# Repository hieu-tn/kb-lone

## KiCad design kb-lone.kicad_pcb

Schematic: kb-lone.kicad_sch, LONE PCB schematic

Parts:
C1, C3, C17, C18: 100n; C_0805_2012Metric
C2: 10u; C_0805_2012Metric
C4, C5: 1u; C_0805_2012Metric
C6, C7, C8, C14, C15: 100n; C_0402_1005Metric
C9, C10: 12p; C_0402_1005Metric
C11, C16: 4.7u; C_0402_1005Metric
C12: 10n; C_0402_1005Metric
C13: 10u; CP_EIA-3216-10_Kemet-I_Pad1.58x1.35mm_HandSolder
C19, C20, C21, C22, C23, C24, C25, C26, C27, C28, C29, C30, C31, C32, C33, C34, C35, C36, C37, C38, C39, C40, C41, C42, C43, C44, C45, C46, C47, C48, C49, C50, C51, C52, C53, C54, C55, C56, C57, C58, C59, C60, C61, C62, C63, C64, C65, C66, C67, C68, C69, C70, C71, C72, C73, C74, C75, C76, C77, C78, C79, C80, C81, C82, C83, C84, C85, C86, C87, C88, C89, C90, C91, C92, C93, C94, C95, C96, C97, C98, C99, C100: 100n; C_0402_1005Metric_1
D1, D3, D4, D5, D6, D7, D8, D9, D10, D11, D12, D13, D14, D15, D16, D17, D18, D19, D20, D21, D22, D23, D24, D25, D26, D27, D28, D29, D30, D31, D32, D33, D34, D35, D36, D37, D38, D39, D40, D41, D42, D43, D44, D45, D46, D47, D48, D49, D50, D51, D52, D53, D54, D55, D56, D57, D58, D59, D60, D61, D62, D63, D64, D65, D66, D67, D68, D69, D70, D71, D72, D73, D74, D75, D76, D77, D78, D79, D80, D81, D82, D83, D84: 1N4148W; D_SOD-123
D2: RB060M-60TR; D_SOD-123; Manufacturer Part Number RB060M-60TR
D85, D86, D87, D88, D89, D90, D91, D92, D93, D94, D95, D96, D97, D98, D99, D100, D101, D102, D103, D104, D105, D106, D107, D108, D109, D110, D111, D112, D113, D114, D115, D116, D117, D118, D119, D120, D121, D122, D123, D124, D125, D126, D127, D128, D129, D130, D131, D132, D133, D134, D135, D136, D137, D138, D139, D140, D141, D142, D143, D144, D145, D146, D147, D148, D149, D150, D151, D152, D153, D154, D155, D156, D157, D158, D159, D160, D161, D162, D163, D164, D165, D166: SK6812MINI-E; SK6812MINI_3535_6028_3.2x2.8mm_Round; Manufacturer Part Number SK812MINI-E
F1: mSMD110-16V; Fuse_1812_4532Metric; Manufacturer Part Number mSMD110-16V
FB1, FB2: CBW201209U121T; L_0805_2012Metric; Manufacturer Part Number CBW201209U121T
H1, H2, H3, H4, H5, H6, H7, H8: 9774035243R; Manufacturer Part Number 9774030243R
H9: MountingHole; MountingHole_2.5x4.0mm
J1: TYPE-C-31-M12; TYPE-C-31-M-12; Manufacturer Part Number TYPE-C-31-M-12
J2, J3: SM04B-SRSS-TB(LF)(SN); SM04B-SRSS-TB(LF)(SN)_mounting-reliefs; Manufacturer Part Number SM04B-SRSS-TB(LF)(SN)
J4: SSD1306
M1: RGB DB notch; rgb_daughterboard_notch_plated_8x4mm
Q1: DTC123JKAT146; SOT-23; Manufacturer Part Number DTC123JKAT146
R1, R2: 5.1k; R_0805_2012Metric
R3: 100R; R_0805_2012Metric
R4: 330k; R_0805_2012Metric
R5: 1M; R_0805_2012Metric
R6, R7: 100k; R_0805_2012Metric
R8, R12, R14: 10k; R_0805_2012Metric
R9, R10: 4.7k; R_0402_1005Metric
R11: 4.7k; R_0805_2012Metric
R13: 1.5k; R_0402_1005Metric
R15, R16, R17, R18, R19, R20, R21, R22, R23, R24, R25, R26, R27, R28, R29, R30, R31, R32, R33, R34, R35, R36, R37, R38, R39, R40, R41, R42, R43, R44, R45, R46, R47, R48, R49, R50, R51, R52, R53, R54, R55, R56, R57, R58, R59, R60, R61, R62, R63, R64, R65, R66, R67, R68, R69, R70, R71, R72, R73, R74, R75, R76, R77, R78, R79, R80, R81, R82, R83, R84, R85, R86, R87, R88, R89, R90, R91, R92, R93, R94, R95, R96: 5.1R; R_0402_1005Metric_1
SW1: K2-1187SQ-A4SW-06; Manufacturer Part Number K2-1187SQ-A4SW-06
SW2: ESC; MX100H; Manufacturer Part Number CPG151101S11
SW3: F1; MX100H; Manufacturer Part Number CPG151101S11
SW4: F2; MX100H; Manufacturer Part Number CPG151101S11
SW5: F3; MX100H; Manufacturer Part Number CPG151101S11
SW6: F4; MX100H; Manufacturer Part Number CPG151101S11
SW7: F5; MX100H; Manufacturer Part Number CPG151101S11
SW8: F6; MX100H; Manufacturer Part Number CPG151101S11
SW9: F7; MX100H; Manufacturer Part Number CPG151101S11
SW10: F8; MX100H; Manufacturer Part Number CPG151101S11
SW11: F9; MX100H; Manufacturer Part Number CPG151101S11
SW12: F10; MX100H; Manufacturer Part Number CPG151101S11
SW13: F11; MX100H; Manufacturer Part Number CPG151101S11
SW14: F12; MX100H; Manufacturer Part Number CPG151101S11
SW15: KNOB; MXA100; Manufacturer Part Number CPG151101S11
SW16: GRV; MX100H; Manufacturer Part Number CPG151101S11
SW17: 1; MX100H; Manufacturer Part Number CPG151101S11
SW18: 2; MX100H; Manufacturer Part Number CPG151101S11
SW19: 3; MX100H; Manufacturer Part Number CPG151101S11
SW20: 4; MX100H; Manufacturer Part Number CPG151101S11
SW21: 5; MX100H; Manufacturer Part Number CPG151101S11
SW22: 6; MX100H; Manufacturer Part Number CPG151101S11
SW23: 7; MX100H; Manufacturer Part Number CPG151101S11
SW24: 8; MX100H; Manufacturer Part Number CPG151101S11
SW25: 9; MX100H; Manufacturer Part Number CPG151101S11
SW26: 0; MX100H; Manufacturer Part Number CPG151101S11
SW27: MINUS; MX100H; Manufacturer Part Number CPG151101S11
SW28: EQUAL; MX100H; Manufacturer Part Number CPG151101S11
SW29: BSPC; MX200H; Manufacturer Part Number CPG151101S11
SW30, SW45: N/A; MX100H; Manufacturer Part Number CPG151101S11
SW31: TAB; MX150H; Manufacturer Part Number CPG151101S11
SW32: Q; MX100H; Manufacturer Part Number CPG151101S11
SW33: W; MX100H; Manufacturer Part Number CPG151101S11
SW34: E; MX100H; Manufacturer Part Number CPG151101S11
SW35: R; MX100H; Manufacturer Part Number CPG151101S11
SW36: T; MX100H; Manufacturer Part Number CPG151101S11
SW37: Y; MX100H; Manufacturer Part Number CPG151101S11
SW38: U; MX100H; Manufacturer Part Number CPG151101S11
SW39: I; MX100H; Manufacturer Part Number CPG151101S11
SW40: O; MX100H; Manufacturer Part Number CPG151101S11
SW41: P; MX100H; Manufacturer Part Number CPG151101S11
SW42: LBRKT; MX100H; Manufacturer Part Number CPG151101S11
SW43: RBRKT; MX100H; Manufacturer Part Number CPG151101S11
SW44: BSLS; MX150H; Manufacturer Part Number CPG151101S11
SW46: CAPS; MX175H; Manufacturer Part Number CPG151101S11
SW47: A; MX100H; Manufacturer Part Number CPG151101S11
SW48: S; MX100H; Manufacturer Part Number CPG151101S11
SW49: D; MX100H; Manufacturer Part Number CPG151101S11
SW50: F; MX100H; Manufacturer Part Number CPG151101S11
SW51: G; MX100H; Manufacturer Part Number CPG151101S11
SW52: H; MX100H; Manufacturer Part Number CPG151101S11
SW53: J; MX100H; Manufacturer Part Number CPG151101S11
SW54: K; MX100H; Manufacturer Part Number CPG151101S11
SW55: L; MX100H; Manufacturer Part Number CPG151101S11
SW56: COLON; MX100H; Manufacturer Part Number CPG151101S11
SW57: QUOTE; MX100H; Manufacturer Part Number CPG151101S11
SW58: ENTER; MX225HR; Manufacturer Part Number CPG151101S11
SW59: PGUP; MX100H; Manufacturer Part Number CPG151101S11
SW60: LSHFT; MX225H; Manufacturer Part Number CPG151101S11
SW61: Z; MX100H; Manufacturer Part Number CPG151101S11
SW62: X; MX100H; Manufacturer Part Number CPG151101S11
SW63: C; MX100H; Manufacturer Part Number CPG151101S11
SW64: V; MX100H; Manufacturer Part Number CPG151101S11
SW65: B; MX100H; Manufacturer Part Number CPG151101S11
SW66: N; MX100H; Manufacturer Part Number CPG151101S11
SW67: M; MX100H; Manufacturer Part Number CPG151101S11
SW68: COMMA; MX100H; Manufacturer Part Number CPG151101S11
SW69: DOT; MX100H; Manufacturer Part Number CPG151101S11
SW70: SLSH; MX100H; Manufacturer Part Number CPG151101S11
SW71: RSHFT; MX175H; Manufacturer Part Number CPG151101S11
SW72: UP; MX100H; Manufacturer Part Number CPG151101S11
SW73: PGDN; MX100H; Manufacturer Part Number CPG151101S11
SW74: LCTRL; MX125H; Manufacturer Part Number CPG151101S11
SW75: WIN; MX125H; Manufacturer Part Number CPG151101S11
SW76: LALT; MX125H; Manufacturer Part Number CPG151101S11
SW77: SPACE; MX625HR; Manufacturer Part Number CPG151101S11
SW78: RALT; MX100H; Manufacturer Part Number CPG151101S11
SW79: FN; MX100H; Manufacturer Part Number CPG151101S11
SW80: RCTRL; MX100H; Manufacturer Part Number CPG151101S11
SW81: LEFT; MX100H; Manufacturer Part Number CPG151101S11
SW82: DOWN; MX100H; Manufacturer Part Number CPG151101S11
SW83: RIGHT; MX100H; Manufacturer Part Number CPG151101S11
SW84: RotaryEncoder_Switch; PEC11R-4220K-S0024
U1: USBLC6-2SC6; SOT-23-6; Manufacturer Part Number USBLC6-2SC6
U2: MCP1700T-3302E/TT; SOT-23; Manufacturer Part Number MCP1700T-3302E/TT
U3: BL24C256A-SFRC; TSSOP-8_4.4x3mm_P0.65mm; Manufacturer Part Number BL24C256A-SFRC
U4: STM32F401RCT6; LQFP-64_10x10mm_P0.5mm; Manufacturer Part Number STM32F401RBT6
U5: TXS0101DBVR; SOT-23-6; Manufacturer Part Number TXS0101DBVR
X1: USB pins; PinHeader_1x4_P2.54mm_Vertical
Y1: TAXM8M4RFDCET2T; Crystal_SMD_3225-4Pin_3.2x2.5mm; Manufacturer Part Number TAXM8M4RFDCET2T

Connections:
3V3: C3.2, C5.1, C6.2, C7.1, C8.1, C11.2, C12.2, C13.1, C14.2, C15.2, C17.2, D2.2 (A), J4.3 (VCC), R7.1, R9.2, R10.2, R13.1, R14.1, SW1.1 (A), U2.2 (VO), U3.8 (VCC), U4.1 (VBAT), U4.13 (VDDA/VREF+), U4.19 (VDD), U4.32 (VDD), U4.48 (VDD), U4.64 (VDD), U5.1 (VCCA)
5V: C4.1, C18.1, D2.1 (K), F1.2, J2.1, J3.1, R6.1, R11.2, R15.2, R16.2, R17.2, R18.2, R19.2, R20.2, R21.2, R22.2, R23.2, R24.2, R25.2, R26.2, R27.2, R28.2, R29.2, R30.2, R31.2, R32.2, R33.2, R34.2, R35.2, R36.2, R37.2, R38.2, R39.2, R40.2, R41.2, R42.2, R43.2, R44.2, R45.2, R46.2, R47.2, R48.2, R49.2, R50.2, R51.2, R52.2, R53.2, R54.2, R55.2, R56.2, R57.2, R58.2, R59.2, R60.2, R61.2, R62.2, R63.2, R64.2, R65.2, R66.2, R67.2, R68.2, R69.2, R70.2, R71.2, R72.2, R73.2, R74.2, R75.2, R76.2, R77.2, R78.2, R79.2, R80.2, R81.2, R82.2, R83.2, R84.2, R85.2, R86.2, R87.2, R88.2, R89.2, R90.2, R91.2, R92.2, R93.2, R94.2, R95.2, R96.2, U2.3 (VI), U5.6 (VCCB), X1.1
BOOT0: C2.2, R4.2, R5.2, U4.60 (BOOT0)
C0: SW2.2, SW16.2, SW31.2, SW46.2, SW60.2, SW74.2, U4.35 (SPI2_MISO/PB14)
C1: SW3.1, SW17.1, SW32.1, SW47.1, SW75.1, U4.36 (SPI2_MOSI/PB15)
C2: SW4.1, SW18.1, SW33.1, SW48.1, SW61.1, SW76.1, U4.37 (I2S2_MCK/TIM3_CH1/USART6_TX/PC6)
C3: SW5.1, SW19.1, SW34.1, SW49.1, SW62.1, U4.38 (USART6_RX/TIM3_CH2/PC7)
C4: SW6.1, SW20.1, SW35.1, SW50.1, SW63.1, U4.39 (USART6_CK/TIM3_CH3/PC8)
C5: SW7.1, SW21.1, SW36.1, SW51.1, SW64.1, U4.40 (TIM3_CH4/I2S_CKIN/PC9)
C6: SW8.1, SW22.1, SW37.1, SW52.1, SW65.1, SW77.2, U4.41 (USART1_CK/TIM1_CH1/PA8)
C7: SW9.1, SW23.1, SW38.1, SW53.1, SW66.1, U4.43 (USART1_RX/TIM1_CH3/PA10)
C8: SW10.1, SW24.1, SW39.1, SW54.1, SW67.1, U4.52 (SPI3_MISO/PC11)
C9: SW11.1, SW25.1, SW40.1, SW55.1, SW68.1, SW78.2, U4.53 (SPI3_MOSI/PC12)
C10: SW12.1, SW26.1, SW41.1, SW56.1, SW69.1, SW79.1, U4.54 (PD2)
C11: SW13.1, SW27.1, SW42.1, SW57.1, SW70.1, SW80.1, U4.55 (JTDO-SWO/SPI1_SCK/SPI3_SCK/I2C2_SDA/TIM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)
C12: SW14.1, SW28.1, SW43.1, SW58.1, SW71.1, SW81.1, U4.56 (NJTRST/SPI1_MISO/SPI3_MISO/I2C3_SDA/TIM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)
C13: SW29.1, SW44.1, SW72.1, SW82.1, U4.57 (SPI1_MOSI/SPI3_MOSI/TIM3_CH2/PB5)
C14: SW15.1, SW30.1, SW45.1, SW59.1, SW73.1, SW83.1, U4.16 (PA2/USART2_TX)
D+: J2.3, R13.2, U1.3 (I/O2), U4.45 (OTG_FS_DP/USART6_RX/PA12), X1.3
D-: J2.2, U1.1 (I/O1), U4.44 (OTG_FS_DM/TIM1_CH4/USART6_TX/PA11), X1.2
DBUS+: J1.A6 (D+), J1.B6 (D+), U1.4 (I/O2)
DBUS-: J1.A7 (D-), J1.B7 (D-), U1.6 (I/O1)
ENC_A: SW84.A, U4.51 (SPI3_SCK/I2S3_CK/PC10)
ENC_B: SW84.B, U4.50 (JTDI/TIM2_CH1/PA14)
E_PA3: U4.17 (PA3/TIM2_CH4)
E_PA4: U4.20 (PA4/USART2_CK)
E_PA5: U4.21 (PA5/TIM2_CH1/SPI1_SCK)
E_PA6: U4.22 (PA6/TIM3_CH1/SPI1_MISO)
E_PA7: U4.23 (PA7/SPI1_MOSI/TIM3_CH2)
E_PB0: U4.26 (PB0/TIM3_CH3)
E_PB1: U4.27 (PB1/TIM3_CH4)
E_PB9: U4.62 (I2C1_SDA/TIM4_CH4/TIM11_CH1/PB9)
E_PB10: U4.29 (PB10/TIM2_CH3/SPI2_SCK/I2C2_SCL/I2S2_CK)
E_PB12: U4.33 (PB12)
E_PB13: U4.34 (SPI2_SCK/I2S2_CK/PB13)
E_PC4: U4.24 (PC4)
E_PC5: U4.25 (PC5)
E_PC13: U4.2 (PC13)
GNDPWR: FB2.2, H9.1, J1.S (SHIELD)
I2C_CLK: J4.2 (SCL), U4.4 (PC15/OSC32_OUT)
I2C_DAT: J4.1 (SDA), U4.3 (PC14/OSC32_IN)
NRST: C1.1, R3.2, U4.7 (NRST)
unnamed: C16.2, U4.30 (VCAP1)
unnamed: C19.1, D85.1 (VDD), R15.1
unnamed: C20.1, D86.1 (VDD), R16.1
unnamed: C21.1, D87.1 (VDD), R17.1
unnamed: C22.1, D88.1 (VDD), R18.1
unnamed: C23.1, D89.1 (VDD), R19.1
unnamed: C24.1, D90.1 (VDD), R20.1
unnamed: C25.1, D91.1 (VDD), R21.1
unnamed: C26.1, D92.1 (VDD), R22.1
unnamed: C27.1, D93.1 (VDD), R23.1
unnamed: C28.1, D94.1 (VDD), R24.1
unnamed: C29.1, D95.1 (VDD), R25.1
unnamed: C30.1, D96.1 (VDD), R26.1
unnamed: C31.1, D97.1 (VDD), R27.1
unnamed: C32.1, D98.1 (VDD), R28.1
unnamed: C33.1, D99.1 (VDD), R29.1
unnamed: C34.1, D100.1 (VDD), R30.1
unnamed: C35.1, D101.1 (VDD), R31.1
unnamed: C36.1, D102.1 (VDD), R32.1
unnamed: C37.1, D103.1 (VDD), R33.1
unnamed: C38.1, D104.1 (VDD), R34.1
unnamed: C39.1, D105.1 (VDD), R35.1
unnamed: C40.1, D106.1 (VDD), R36.1
unnamed: C41.1, D107.1 (VDD), R37.1
unnamed: C42.1, D108.1 (VDD), R38.1
unnamed: C43.1, D109.1 (VDD), R39.1
unnamed: C44.1, D110.1 (VDD), R40.1
unnamed: C45.1, D111.1 (VDD), R41.1
unnamed: C46.1, D112.1 (VDD), R42.1
unnamed: C47.1, D113.1 (VDD), R43.1
unnamed: C48.1, D114.1 (VDD), R44.1
unnamed: C49.1, D115.1 (VDD), R45.1
unnamed: C50.1, D116.1 (VDD), R46.1
unnamed: C51.1, D117.1 (VDD), R47.1
unnamed: C52.1, D118.1 (VDD), R48.1
unnamed: C53.1, D119.1 (VDD), R49.1
unnamed: C54.1, D120.1 (VDD), R50.1
unnamed: C55.1, D121.1 (VDD), R51.1
unnamed: C56.1, D122.1 (VDD), R52.1
unnamed: C57.1, D123.1 (VDD), R53.1
unnamed: C58.1, D124.1 (VDD), R54.1
unnamed: C59.1, D125.1 (VDD), R55.1
unnamed: C60.1, D126.1 (VDD), R56.1
unnamed: C61.1, D127.1 (VDD), R57.1
unnamed: C62.1, D128.1 (VDD), R58.1
unnamed: C63.1, D129.1 (VDD), R59.1
unnamed: C64.1, D130.1 (VDD), R60.1
unnamed: C65.1, D131.1 (VDD), R61.1
unnamed: C66.1, D132.1 (VDD), R62.1
unnamed: C67.1, D133.1 (VDD), R63.1
unnamed: C68.1, D134.1 (VDD), R64.1
unnamed: C69.1, D135.1 (VDD), R65.1
unnamed: C70.1, D136.1 (VDD), R66.1
unnamed: C71.1, D137.1 (VDD), R67.1
unnamed: C72.1, D138.1 (VDD), R68.1
unnamed: C73.1, D139.1 (VDD), R69.1
unnamed: C74.1, D140.1 (VDD), R70.1
unnamed: C75.1, D141.1 (VDD), R71.1
unnamed: C76.1, D142.1 (VDD), R72.1
unnamed: C77.1, D143.1 (VDD), R73.1
unnamed: C78.1, D144.1 (VDD), R74.1
unnamed: C79.1, D145.1 (VDD), R75.1
unnamed: C80.1, D146.1 (VDD), R76.1
unnamed: C81.1, D147.1 (VDD), R77.1
unnamed: C82.1, D148.1 (VDD), R78.1
unnamed: C83.1, D149.1 (VDD), R79.1
unnamed: C84.1, D150.1 (VDD), R80.1
unnamed: C85.1, D151.1 (VDD), R81.1
unnamed: C86.1, D152.1 (VDD), R82.1
unnamed: C87.1, D153.1 (VDD), R83.1
unnamed: C88.1, D154.1 (VDD), R84.1
unnamed: C89.1, D155.1 (VDD), R85.1
unnamed: C90.1, D156.1 (VDD), R86.1
unnamed: C91.1, D157.1 (VDD), R87.1
unnamed: C92.1, D158.1 (VDD), R88.1
unnamed: C93.1, D159.1 (VDD), R89.1
unnamed: C94.1, D160.1 (VDD), R90.1
unnamed: C95.1, D161.1 (VDD), R91.1
unnamed: C96.1, D162.1 (VDD), R92.1
unnamed: C97.1, D163.1 (VDD), R93.1
unnamed: C98.1, D164.1 (VDD), R94.1
unnamed: C99.1, D165.1 (VDD), R95.1
unnamed: C100.1, D166.1 (VDD), R96.1
unnamed: D1.1 (K), R4.1
unnamed: D1.2 (A), Q1.1 (B), SW1.2 (B)
unnamed: D3.2 (A), SW2.1
unnamed: D4.2 (A), SW3.2
unnamed: D5.2 (A), SW4.2
unnamed: D6.2 (A), SW5.2
unnamed: D7.2 (A), SW6.2
unnamed: D8.2 (A), SW7.2
unnamed: D9.2 (A), SW8.2
unnamed: D10.2 (A), SW9.2
unnamed: D11.2 (A), SW10.2
unnamed: D12.2 (A), SW11.2
unnamed: D13.2 (A), SW12.2
unnamed: D14.2 (A), SW13.2
unnamed: D15.2 (A), SW14.2
unnamed: D17.2 (A), SW16.1
unnamed: D18.2 (A), SW17.2
unnamed: D19.2 (A), SW18.2
unnamed: D20.2 (A), SW19.2
unnamed: D21.2 (A), SW20.2
unnamed: D22.2 (A), SW21.2
unnamed: D23.2 (A), SW22.2
unnamed: D24.2 (A), SW23.2
unnamed: D25.2 (A), SW24.2
unnamed: D26.2 (A), SW25.2
unnamed: D27.2 (A), SW26.2
unnamed: D28.2 (A), SW27.2
unnamed: D29.2 (A), SW28.2
unnamed: D30.2 (A), SW29.2
unnamed: D31.2 (A), SW30.2
unnamed: D32.2 (A), SW31.1
unnamed: D33.2 (A), SW32.2
unnamed: D34.2 (A), SW33.2
unnamed: D35.2 (A), SW34.2
unnamed: D36.2 (A), SW35.2
unnamed: D37.2 (A), SW36.2
unnamed: D38.2 (A), SW37.2
unnamed: D39.2 (A), SW38.2
unnamed: D40.2 (A), SW39.2
unnamed: D41.2 (A), SW40.2
unnamed: D42.2 (A), SW41.2
unnamed: D43.2 (A), SW42.2
unnamed: D44.2 (A), SW43.2
unnamed: D45.2 (A), SW44.2
unnamed: D46.2 (A), SW45.2
unnamed: D47.2 (A), SW46.1
unnamed: D48.2 (A), SW47.2
unnamed: D49.2 (A), SW48.2
unnamed: D50.2 (A), SW49.2
unnamed: D51.2 (A), SW50.2
unnamed: D52.2 (A), SW51.2
unnamed: D53.2 (A), SW52.2
unnamed: D54.2 (A), SW53.2
unnamed: D55.2 (A), SW54.2
unnamed: D56.2 (A), SW55.2
unnamed: D57.2 (A), SW56.2
unnamed: D58.2 (A), SW57.2
unnamed: D59.2 (A), SW58.2
unnamed: D60.2 (A), SW59.2
unnamed: D61.2 (A), SW60.1
unnamed: D62.2 (A), SW61.2
unnamed: D63.2 (A), SW62.2
unnamed: D64.2 (A), SW63.2
unnamed: D65.2 (A), SW64.2
unnamed: D66.2 (A), SW65.2
unnamed: D67.2 (A), SW66.2
unnamed: D68.2 (A), SW67.2
unnamed: D69.2 (A), SW68.2
unnamed: D70.2 (A), SW69.2
unnamed: D71.2 (A), SW70.2
unnamed: D72.2 (A), SW71.2
unnamed: D73.2 (A), SW72.2
unnamed: D74.2 (A), SW73.2
unnamed: D75.2 (A), SW74.1
unnamed: D76.2 (A), SW75.2
unnamed: D77.2 (A), SW76.2
unnamed: D78.2 (A), SW77.1
unnamed: D79.2 (A), SW78.1
unnamed: D80.2 (A), SW79.2
unnamed: D81.2 (A), SW80.2
unnamed: D82.2 (A), SW81.2
unnamed: D83.2 (A), SW82.2
unnamed: D84.2 (A), SW83.2
unnamed: D85.2 (DOUT), D99.4 (DIN)
unnamed: D85.4 (DIN), D86.2 (DOUT)
unnamed: D86.4 (DIN), D87.2 (DOUT)
unnamed: D87.4 (DIN), D88.2 (DOUT)
unnamed: D88.4 (DIN), D89.2 (DOUT)
unnamed: D89.4 (DIN), D90.2 (DOUT)
unnamed: D90.4 (DIN), D91.2 (DOUT)
unnamed: D91.4 (DIN), D92.2 (DOUT)
unnamed: D92.4 (DIN), D93.2 (DOUT)
unnamed: D93.4 (DIN), D94.2 (DOUT)
unnamed: D94.4 (DIN), D95.2 (DOUT)
unnamed: D95.4 (DIN), D96.2 (DOUT)
unnamed: D96.4 (DIN), D97.2 (DOUT)
unnamed: D97.4 (DIN), D98.2 (DOUT)
unnamed: D100.2 (DOUT), D101.4 (DIN)
unnamed: D99.2 (DOUT), D100.4 (DIN)
unnamed: D101.2 (DOUT), D102.4 (DIN)
unnamed: D102.2 (DOUT), D103.4 (DIN)
unnamed: D103.2 (DOUT), D104.4 (DIN)
unnamed: D104.2 (DOUT), D105.4 (DIN)
unnamed: D105.2 (DOUT), D106.4 (DIN)
unnamed: D106.2 (DOUT), D107.4 (DIN)
unnamed: D107.2 (DOUT), D108.4 (DIN)
unnamed: D108.2 (DOUT), D109.4 (DIN)
unnamed: D109.2 (DOUT), D110.4 (DIN)
unnamed: D110.2 (DOUT), D111.4 (DIN)
unnamed: D111.2 (DOUT), D112.4 (DIN)
unnamed: D112.2 (DOUT), D113.4 (DIN)
unnamed: D113.2 (DOUT), D128.4 (DIN)
unnamed: D114.2 (DOUT), D129.4 (DIN)
unnamed: D114.4 (DIN), D115.2 (DOUT)
unnamed: D115.4 (DIN), D116.2 (DOUT)
unnamed: D116.4 (DIN), D117.2 (DOUT)
unnamed: D117.4 (DIN), D118.2 (DOUT)
unnamed: D118.4 (DIN), D119.2 (DOUT)
unnamed: D119.4 (DIN), D120.2 (DOUT)
unnamed: D120.4 (DIN), D121.2 (DOUT)
unnamed: D121.4 (DIN), D122.2 (DOUT)
unnamed: D122.4 (DIN), D123.2 (DOUT)
unnamed: D123.4 (DIN), D124.2 (DOUT)
unnamed: D124.4 (DIN), D125.2 (DOUT)
unnamed: D125.4 (DIN), D126.2 (DOUT)
unnamed: D126.4 (DIN), D127.2 (DOUT)
unnamed: D127.4 (DIN), D128.2 (DOUT)
unnamed: D129.2 (DOUT), D130.4 (DIN)
unnamed: D130.2 (DOUT), D131.4 (DIN)
unnamed: D131.2 (DOUT), D132.4 (DIN)
unnamed: D132.2 (DOUT), D133.4 (DIN)
unnamed: D133.2 (DOUT), D134.4 (DIN)
unnamed: D134.2 (DOUT), D135.4 (DIN)
unnamed: D135.2 (DOUT), D136.4 (DIN)
unnamed: D136.2 (DOUT), D137.4 (DIN)
unnamed: D137.2 (DOUT), D138.4 (DIN)
unnamed: D138.2 (DOUT), D139.4 (DIN)
unnamed: D139.2 (DOUT), D140.4 (DIN)
unnamed: D140.2 (DOUT), D141.4 (DIN)
unnamed: D141.2 (DOUT), D142.4 (DIN)
unnamed: D142.2 (DOUT), D156.4 (DIN)
unnamed: D143.2 (DOUT), D157.4 (DIN)
unnamed: D143.4 (DIN), D144.2 (DOUT)
unnamed: D144.4 (DIN), D145.2 (DOUT)
unnamed: D145.4 (DIN), D146.2 (DOUT)
unnamed: D146.4 (DIN), D147.2 (DOUT)
unnamed: D147.4 (DIN), D148.2 (DOUT)
unnamed: D148.4 (DIN), D149.2 (DOUT)
unnamed: D149.4 (DIN), D150.2 (DOUT)
unnamed: D150.4 (DIN), D151.2 (DOUT)
unnamed: D151.4 (DIN), D152.2 (DOUT)
unnamed: D152.4 (DIN), D153.2 (DOUT)
unnamed: D153.4 (DIN), D154.2 (DOUT)
unnamed: D154.4 (DIN), D155.2 (DOUT)
unnamed: D155.4 (DIN), D156.2 (DOUT)
unnamed: D157.2 (DOUT), D158.4 (DIN)
unnamed: D158.2 (DOUT), D159.4 (DIN)
unnamed: D159.2 (DOUT), D160.4 (DIN)
unnamed: D160.2 (DOUT), D161.4 (DIN)
unnamed: D161.2 (DOUT), D162.4 (DIN)
unnamed: D162.2 (DOUT), D163.4 (DIN)
unnamed: D163.2 (DOUT), D164.4 (DIN)
unnamed: D164.2 (DOUT), D165.4 (DIN)
unnamed: D165.2 (DOUT), D166.4 (DIN)
unnamed: FB1.1, H1.1
unnamed: J1.A5 (CC1), R1.2
unnamed: J1.B5 (CC2), R2.2
unnamed: Q1.3 (C), R3.1
unnamed: R14.2, U5.5 (OE)
OSC1: C9.2, U4.5 (PH0/OSC_IN), Y1.1
OSC2: C10.1, U4.6 (PH1/OSC_OUT), Y1.3
PA9: R11.1, R12.1, U4.42 (USART1_TX/TIM1_CH2/PA9)
PB2/BOOT1: R8.1, U4.28 (PB2)
R0: D3.1 (K), D4.1 (K), D5.1 (K), D6.1 (K), D7.1 (K), D8.1 (K), D9.1 (K), D10.1 (K), D11.1 (K), D12.1 (K), D13.1 (K), D14.1 (K), D15.1 (K), D16.1 (K), U4.8 (PC0)
R1: D17.1 (K), D18.1 (K), D19.1 (K), D20.1 (K), D21.1 (K), D22.1 (K), D23.1 (K), D24.1 (K), D25.1 (K), D26.1 (K), D27.1 (K), D28.1 (K), D29.1 (K), D30.1 (K), D31.1 (K), U4.9 (PC1)
R2: D32.1 (K), D33.1 (K), D34.1 (K), D35.1 (K), D36.1 (K), D37.1 (K), D38.1 (K), D39.1 (K), D40.1 (K), D41.1 (K), D42.1 (K), D43.1 (K), D44.1 (K), D45.1 (K), D46.1 (K), U4.10 (PC2/SPI2_MISO)
R3: D47.1 (K), D48.1 (K), D49.1 (K), D50.1 (K), D51.1 (K), D52.1 (K), D53.1 (K), D54.1 (K), D55.1 (K), D56.1 (K), D57.1 (K), D58.1 (K), D59.1 (K), D60.1 (K), U4.11 (PC3/SPI2_MOSI)
R4: D61.1 (K), D62.1 (K), D63.1 (K), D64.1 (K), D65.1 (K), D66.1 (K), D67.1 (K), D68.1 (K), D69.1 (K), D70.1 (K), D71.1 (K), D72.1 (K), D73.1 (K), D74.1 (K), U4.14 (PA0/TIM2_CH1/USART2_CTS)
R5: D75.1 (K), D76.1 (K), D77.1 (K), D78.1 (K), D79.1 (K), D80.1 (K), D81.1 (K), D82.1 (K), D83.1 (K), D84.1 (K), U4.15 (PA1/TIM2_CH2/USART2_RTS)
RGB_3V3: U4.61 (I2C1_SCL/TIM4_CH3/TIM10_CH1/PB8), U5.3 (A)
RGB_5V: D98.4 (DIN), U5.4 (B)
RGB_OUT: D166.2 (DOUT), J3.3
SCL: R10.1, U3.6 (SCL), U4.58 (I2C1_SCL/USART1_TX/TIM4_CH1/PB6)
SDA: R9.1, U3.5 (SDA), U4.59 (I2C1_SDA/USART1_RX/TIM4_CH2/PB7)
SWDIO: U4.46 (JTMS-SWDIO/PA13)
VBUS: F1.1, J1.A4 (VBUS), J1.B4 (VBUS), U1.5 (VBUS)

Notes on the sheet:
PG UP
EEPROM
SWITCH MATRIX
SLSH
USB CONNECTOR
(*) "Spooky pins": on STM32F4x1, pins A9 and B2 cannot be used for switch matrix: - A9 is meant to be used as a VBUS sensing. It has a undocumented internal pulldown resistor; - B2 is used as BOOT1 during bootup, so it needs an external pulldown for successful bootup
N/A
BSLS
PLATE STANDOFFS
3V3
WIN
SPOOKY PIN
BSPC
CAPS
RCTRL
TAB
(**) PA9 jumper: a solderable jumper used to tie PA9 to VBUS. It is disconnected by default, hence PA9 is left floating
F10
RGB STRIP
RSHFT
RIGHT
MINUS
COLON
RALT
RGV
EXCLUSIVE
HARD RESET
COMMA
LSHFT
ENTER
F12
KNOB
DOWN
LCTRL
PG DN
DOT
LEFT
MCU
SPACE
LBRKT

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
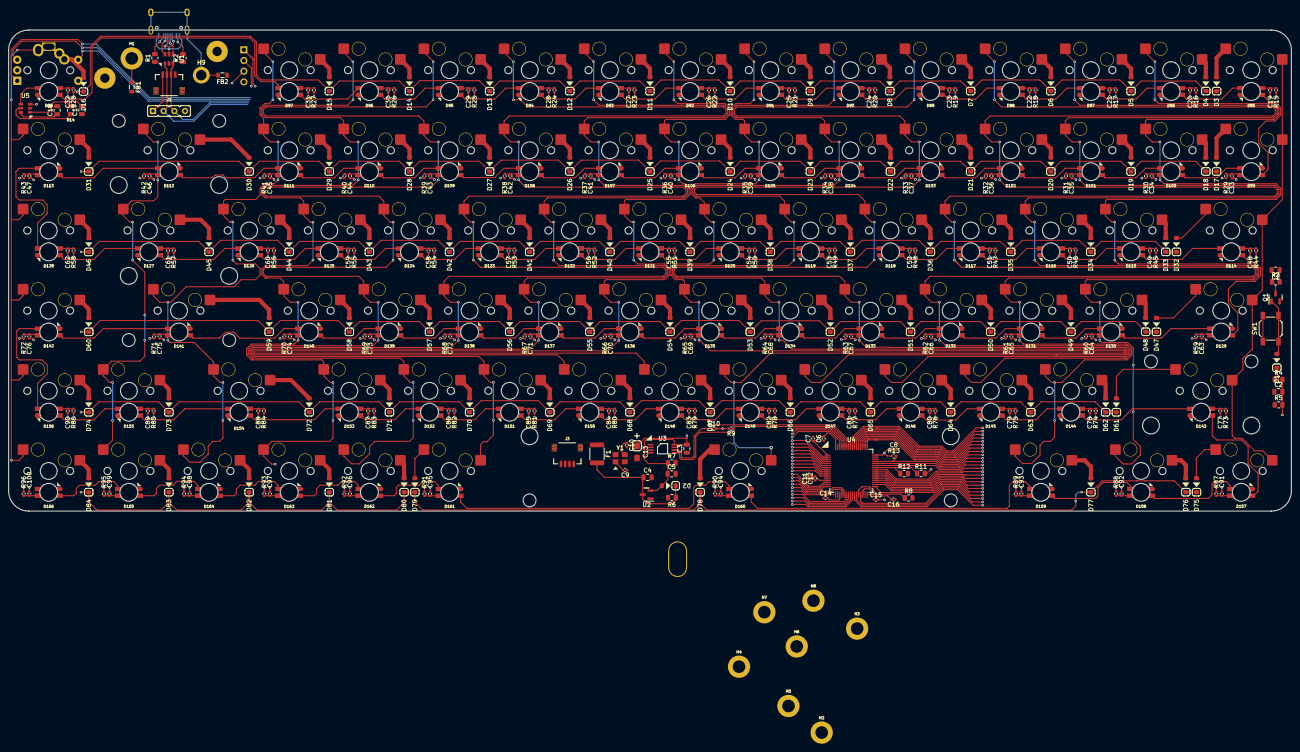
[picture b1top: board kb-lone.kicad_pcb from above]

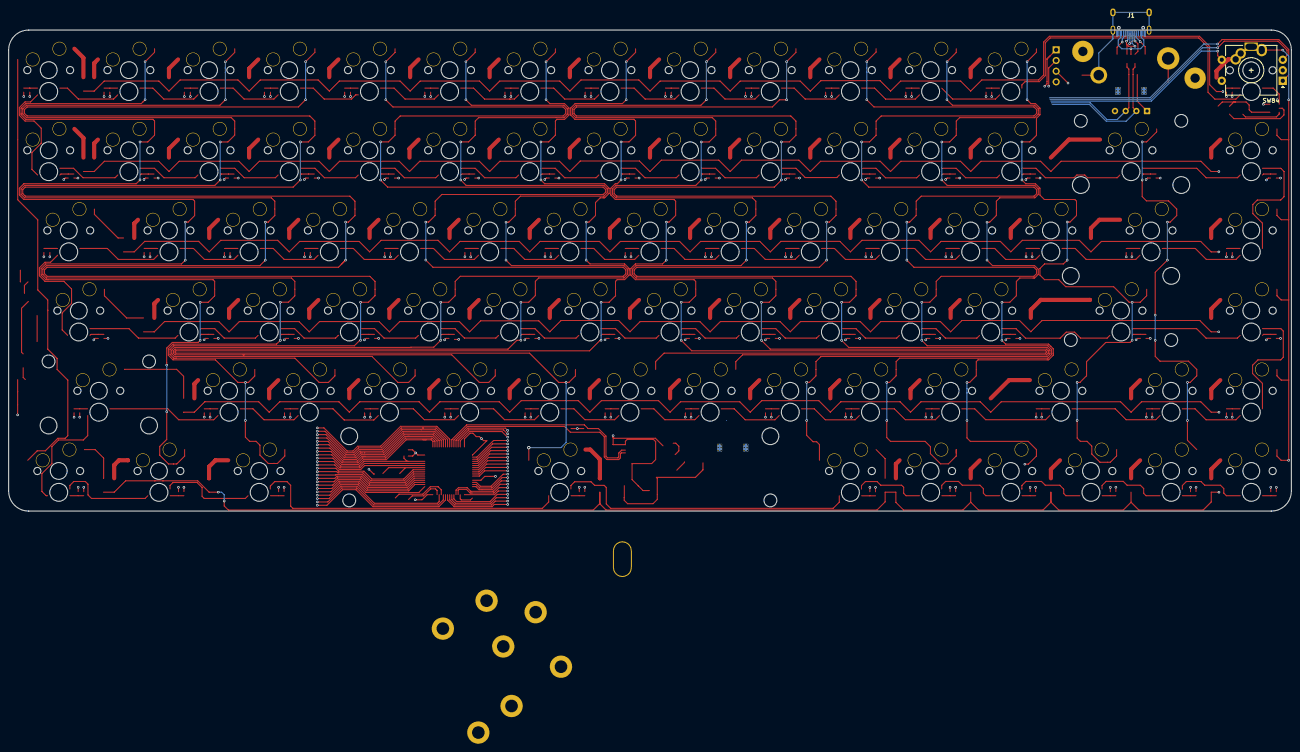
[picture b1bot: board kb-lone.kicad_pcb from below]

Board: 2 copper layers, 304.8 x 114.3 mm, 471 parts (3 on the bottom side), 298 nets.

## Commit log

2022-02-03 init
2022-02-03 add kb layout
2022-02-04 schematics switches
2022-02-05 schematics rgb leds
2022-02-07 place sw + rgb led
2022-02-08 place components
2022-02-10 routing
2022-03-13 fix DRC
2022-03-19 remove redundancy
2022-03-22 add mounting holes
2022-04-22 fix positions
2022-05-04 edge cuts
2022-05-05 track
2022-06-06 fix edge cuts
2022-12-14 assets
2022-12-14 daughter board
2022-12-14 layout
